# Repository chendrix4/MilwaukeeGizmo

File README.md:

Revision 1. Will add more details later.

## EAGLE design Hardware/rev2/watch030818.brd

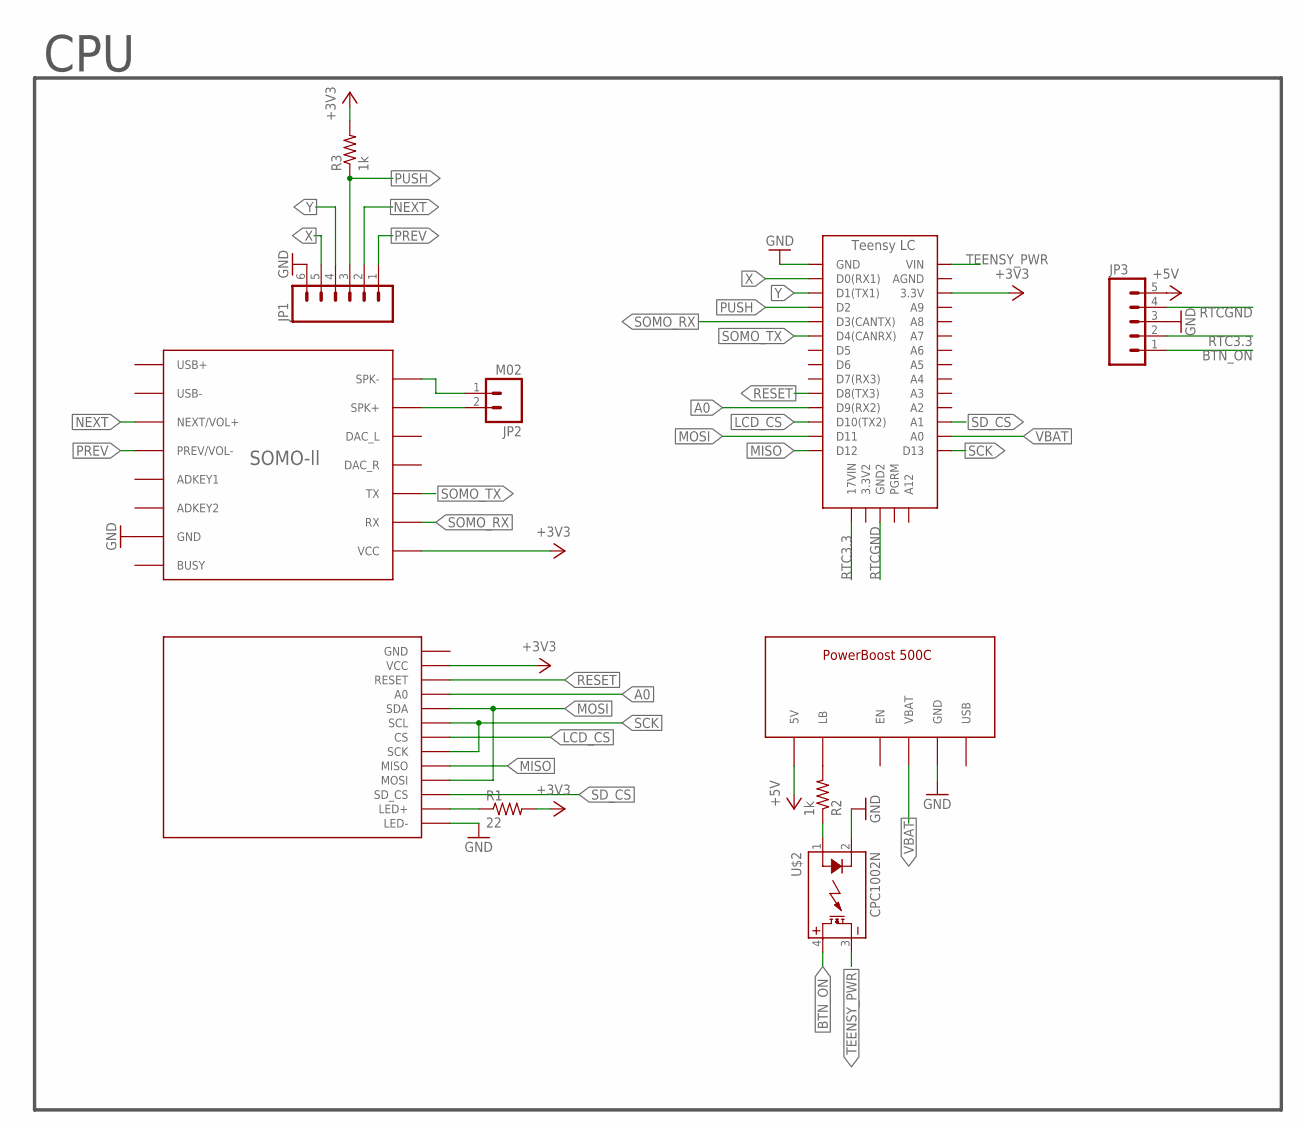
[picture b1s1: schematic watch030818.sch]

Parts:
1.8-SPI-TFT: KMR-1.8_SPI_TFT
JP1: M06; 1X06
JP2: M02; 1X02
JP3: M05; 1X05
R1: 22; 0402-RES
R2, R3: 1k; 0402-RES
U$1: TEENSY_LC
U$2: CPC1002N; SOP04
U$5: POWERBOOST-500C
U$11: SOMO-LL

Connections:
+3V3: 1.8-SPI-TFT.VCC, R1.2, R3.2, U$1.3.3V, U$11.VCC
+5V: JP3.5, U$5.5V
A0: 1.8-SPI-TFT.A0, U$1.D9(RX2)
BTN_ON: JP3.1, U$2.4 (DC+)
GND: 1.8-SPI-TFT.LED-, JP1.6, JP3.3, U$1.GND, U$2.2 (CONTROL-), U$5.GND0 (GND), U$5.GND1 (GND), U$5.GND2 (GND), U$11.GND, U$11.GND@0 (GND)
LB: R2.2, U$5.LB
LCD_CS: 1.8-SPI-TFT.CS, U$1.D10(TX2)
MISO: 1.8-SPI-TFT.MISO, U$1.D12
MOSI: 1.8-SPI-TFT.MOSI, 1.8-SPI-TFT.SDA, U$1.D11
unnamed: 1.8-SPI-TFT.LED+, R1.1
unnamed: R2.1, U$2.1 (CONTROL+)
NEXT: JP1.2, U$11.NEXT/VOL+
PREV: JP1.1, U$11.PREV/VOL-
PUSH: JP1.3, R3.1, U$1.D2
RESET: 1.8-SPI-TFT.RESET, U$1.D8(TX3)
RTC3.3: JP3.2, U$1.17VIN
RTCGND: JP3.4, U$1.GND2
SCK: 1.8-SPI-TFT.SCK, 1.8-SPI-TFT.SCL, U$1.D13
SD_CS: 1.8-SPI-TFT.SD_CS, U$1.A1
SOMO_RX: U$1.D3(CANTX), U$11.RX
SOMO_TX: U$1.D4(CANRX), U$11.TX
SPK_IN: JP2.1, U$11.SPK-
SPK_OUT: JP2.2, U$11.SPK+
TEENSY_PWR: U$1.VIN, U$2.3 (DC-)
VBAT: U$1.A0, U$5.VBAT
X: JP1.5, U$1.D0(RX1)
Y: JP1.4, U$1.D1(TX1)

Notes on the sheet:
CPU

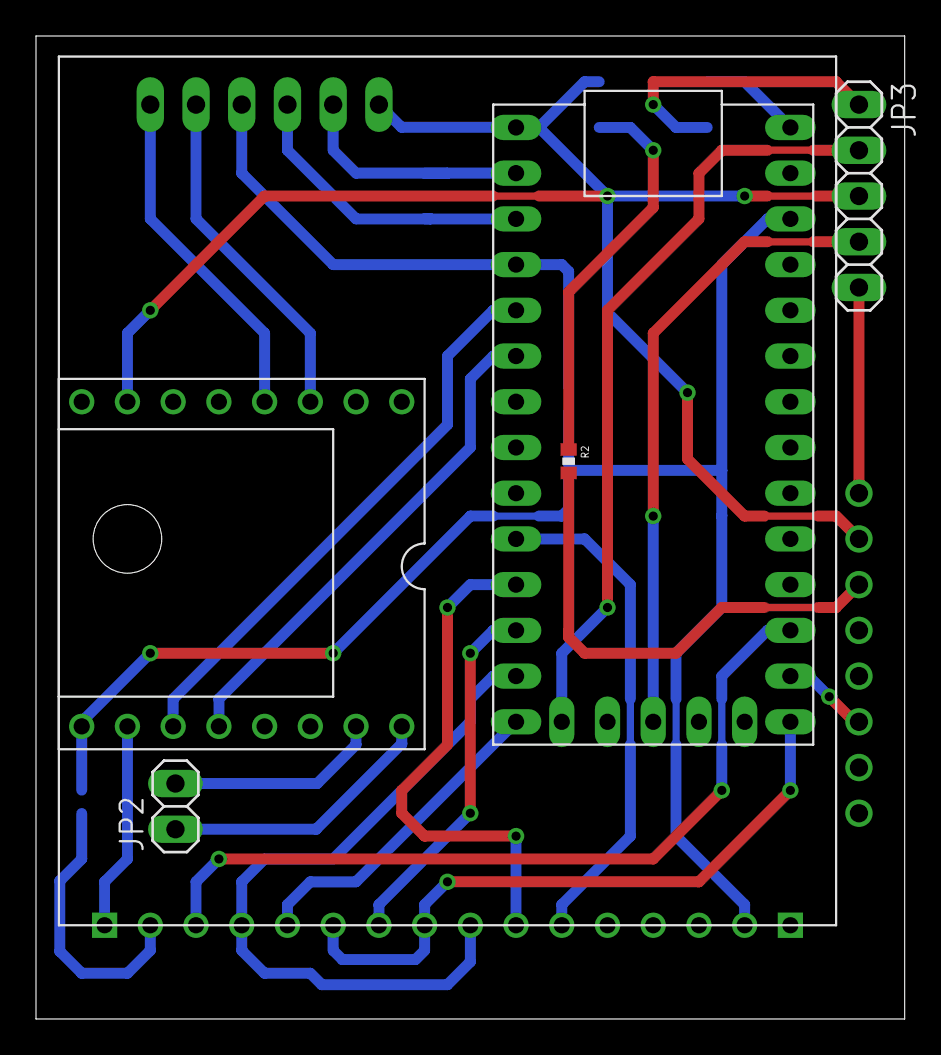
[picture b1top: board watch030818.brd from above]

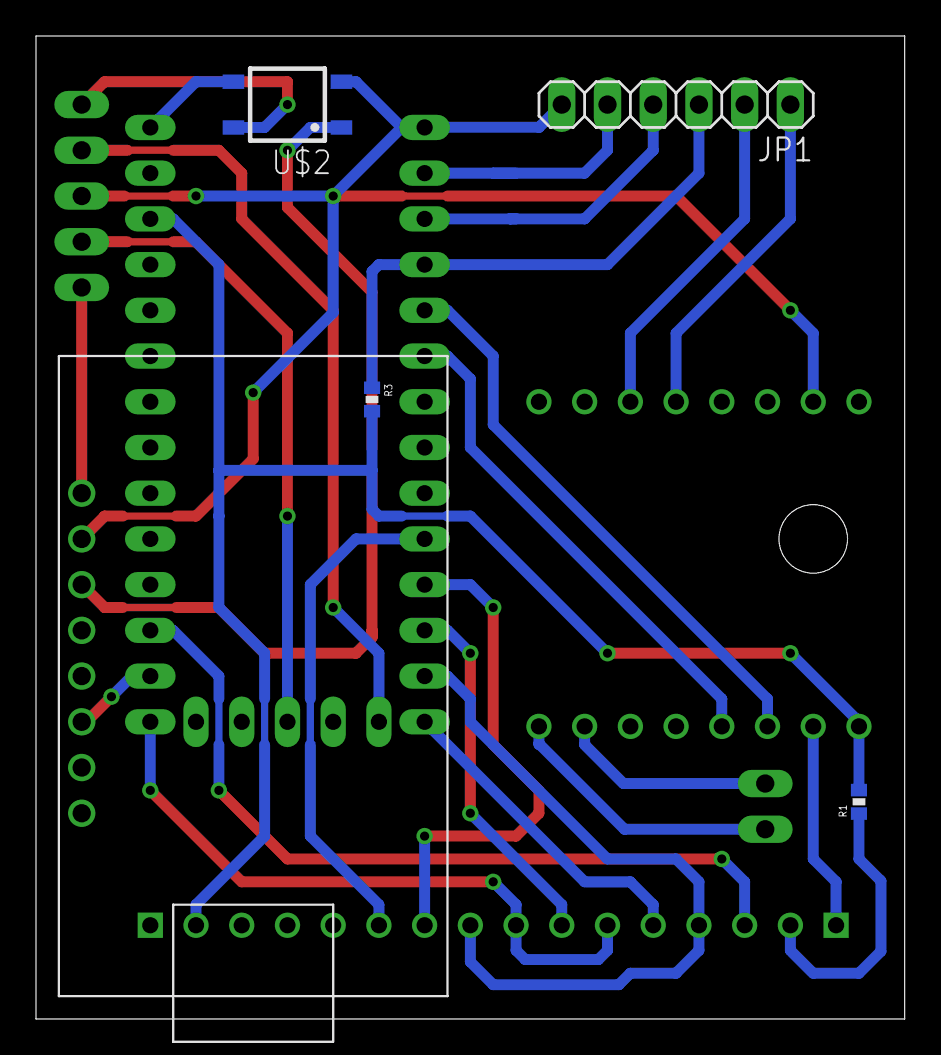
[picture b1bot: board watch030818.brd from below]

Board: 2 copper layers, 48.3 x 54.6 mm, 11 parts (5 on the bottom side), 27 nets.

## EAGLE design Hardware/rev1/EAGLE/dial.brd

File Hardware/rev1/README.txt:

Inventor
watch.ipt -- concept design
lisa.ipt -- actual case with necessary dimensions

Gerber Files
uploaded as zip to JLC for manufacturing

Schematics and boards
side_panels.sch -- button interface overall layout
dial.brd -- rotary dial and vol buttons
power.brd -- power button and coin cell
watch.* -- self-explanatory

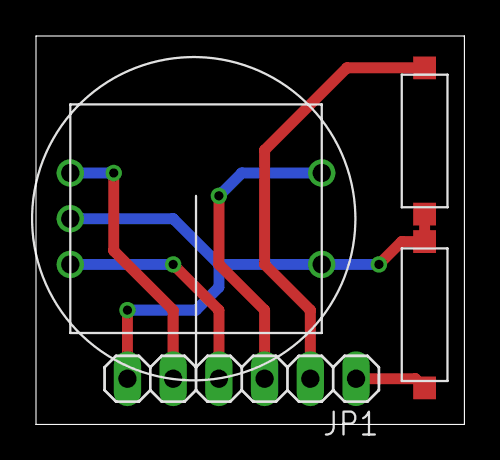
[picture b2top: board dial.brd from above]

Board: 2 copper layers, 23.8 x 21.6 mm, 4 parts (0 on the bottom side), 6 nets.

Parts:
JP1: 1X06
U$3: ROTARY_ENCODER
U$4, U$5: MOM_SPST

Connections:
GND: JP1.6, U$3.GND0, U$3.GND1, U$4.P$1, U$5.P$1
NEXT: JP1.2, U$4.P$2
PREV: JP1.1, U$5.P$2
PUSH: JP1.3, U$3.PUSH
X: JP1.4, U$3.X
Y: JP1.5, U$3.Y

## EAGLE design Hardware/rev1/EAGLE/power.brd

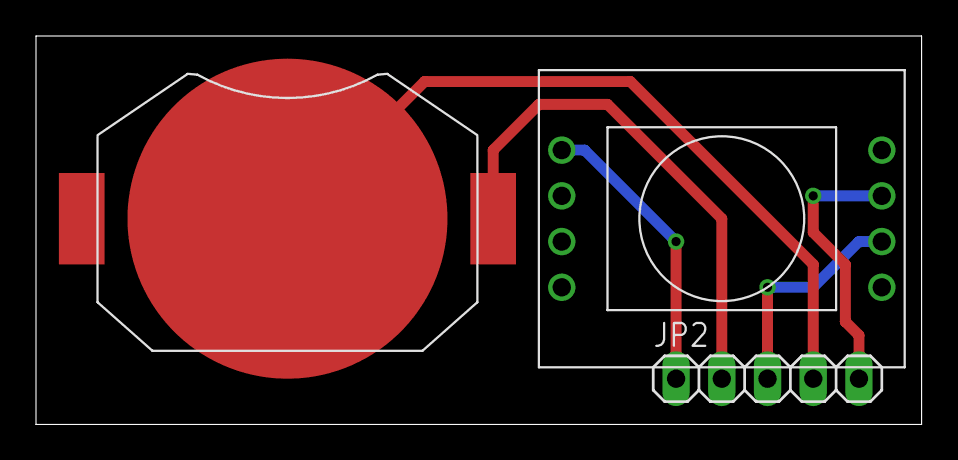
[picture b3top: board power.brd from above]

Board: 2 copper layers, 49.2 x 21.6 mm, 3 parts (0 on the bottom side), 5 nets.

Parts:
JP2: 1X05
U$1: MOMENTARY_PUSH; MOMENTARY_POWER_BUTTON
U$2: CR2032-20MM-CONN

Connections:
5V: JP2.1, U$1.IN@0, U$1.IN@1
BTN_ON: JP2.5, U$1.OUT@0, U$1.OUT@1
GND: JP2.3, U$1.GND@0, U$1.GND@1
RTC3.3: JP2.2, U$2.V+@0, U$2.V+@1
RTCGND: JP2.4, U$2.GND

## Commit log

2018-06-03 Fixed .gitignore issue
